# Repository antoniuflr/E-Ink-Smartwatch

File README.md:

# InkTime Smartwatch
The low-powered open-source e-paper watch.

## Final Assembly

## Block Diagram

## Bill of Materials
| Ref | Componenta | Valoare | JLC Parts | Datasheet |
|-----|------------|---------|-----------|-----------|
| U1 | nRF52840 | $5.14 | [JLC](https://jlcpcb.com/parts/componentSearch?searchTxt=nRF52840-QF) | [DS](https://jlcpcb.com/api/file/downloadByFileSystemAccessId/8589839228197629952) |
| J1 | 503480-2400 | $0.84 | [JLC](https://jlcpcb.com/partdetail/MOLEX-5034802400/C122434) | [DS](https://www.molex.com/content/dam/molex/molex-dot-com/products/automated/en-us/salesdrawingpdf/503/503480/5034802400_sd.pdf?inline) |
| IC1 | BQ25180YBGR | $2.01 | [JLC](https://jlcpcb.com/partdetail/TexasInstruments-BQ25180YBGR/C3682423) | [DS](https://www.ti.com/cn/lit/gpn/bq25180) |
| X2 | FC-135_32.7680KA-A3 | $0.2677 | [JLC](https://jlcpcb.com/partdetail/SeikoEpson-FC_135_32_7680KAA3/C2650472) | [DS](https://jlcpcb.com/partdetail/SeikoEpson-FC_135_32_7680KAA3/C2650472) |
| Q1 | DMG2305UX-7 | $0.10 | [JLC](https://jlcpcb.com/partdetail/DiodesIncorporated-DMG2305UX7/C150470) | [DS](https://jlcpcb.com/api/file/downloadByFileSystemAccessId/8560079443617075200) |
| D5 | MBR0530 | $0.03 | [JLC](https://jlcpcb.com/partdetail/78464-MBR0530/C77336) | [DS](https://jlcpcb.com/api/file/downloadByFileSystemAccessId/8586175081181818880) |
| IC9 | RT6160 | $0.56 | [JLC](https://jlcpcb.com/partdetail/RichtekTech-RT6160AWSC/C7065276) | [DS](https://jlcpcb.com/api/file/downloadByFileSystemAccessId/8600398231234883584) |
| L2 | RC0402JR-070RL | $0.01 | [JLC](https://jlcpcb.com/partdetail/YAGEO-RC0402JR070RL/C60485) | [DS](https://jlcpcb.com/api/file/downloadByFileSystemAccessId/8717146932348461056) |
| J4 | KH-TYPE-C-16P | $0.08 | [JLC](https://jlcpcb.com/partdetail/Shenzhen_KinghelmElec-KH_TYPE_C16P/C709357) | [DS](https://jlcpcb.com/api/file/downloadByFileSystemAccessId/8588905154556923904) |
| SWD | TC2030-IDC | $100.26 | [JLC](https://jlcpcb.com/partdetail/MicrochipTech-TC2030_CLIP3PACK/C5444772) | [DS](https://www.lcsc.com/datasheet/lcsc_datasheet_2403201318_Microchip-Tech-TC2030-CLIP-3PACK_C5444772.pdf) |
| U3 | MAX17048G-T10 | $2.44 | [JLC](https://jlcpcb.com/partdetail/2777647-MAX17048GT10/C2682616) | [DS](https://jlcpcb.com/api/file/downloadByFileSystemAccessId/8588907428524003328) |
| D3 | USBLC6-2SC6Y | $0.24 | [JLC](https://jlcpcb.com/partdetail/STMicroelectronics-USBLC62SC6Y/C2969755) | [DS](https://jlcpcb.com/api/file/downloadByFileSystemAccessId/8603165824304111616) |
| L3 | RC0402JR-070RL | $0.01 | [JLC](https://jlcpcb.com/partdetail/YAGEO-RC0402JR070RL/C60485) | [DS](https://jlcpcb.com/api/file/downloadByFileSystemAccessId/8717146932348461056) |
| X1 | NX2016SA-32MHZ-EXS00A-CS11336 | $9.04 | [JLC](https://jlcpcb.com/partdetail/NDK-NX2016SA_32MHZ_EXS00ACS11336/C6134317) | [DS](https://jlcpcb.com/api/file/downloadByFileSystemAccessId/8603064888214908928) |
| ANT1 | 2450AT18B100E | $1.03 | [JLC](https://jlcpcb.com/partdetail/JohansonDielectrics-2450AT18B100E/C2917717) | [DS](https://jlcpcb.com/api/file/downloadByFileSystemAccessId/8588940948130156544) |
| Q3 | SI1308EDL-T1-GE3 | $0.18 | [JLC](https://jlcpcb.com/partdetail/VishayIntertech-SI1308EDL_T1GE3/C469327) | [DS](https://jlcpcb.com/api/file/downloadByFileSystemAccessId/8588884784742846464) |
| IC2 | DRV2605YZFR | $1.31 | [JLC](https://jlcpcb.com/partdetail/TexasInstruments-DRV2605YZFR/C81079) | [DS](https://www.ti.com/cn/lit/gpn/drv2605) |
| D2 | MBR0530 | $0.03 | [JLC](https://jlcpcb.com/partdetail/78464-MBR0530/C77336) | [DS](https://jlcpcb.com/api/file/downloadByFileSystemAccessId/8586175081181818880) |
| IC3 | BMA423 | $11.30 | [JLC](https://jlcpcb.com/partdetail/BoschSensortec-BMA423/C189517) | [DS](https://jlcpcb.com/api/file/downloadByFileSystemAccessId/8588894317147017216) |
| L7 | MLP2016SR47MT0S1 | $0.10 | [JLC](https://jlcpcb.com/partdetail/TDK-MLP2016SR47MT0S1/C87545) | [DS](https://jlcpcb.com/api/file/downloadByFileSystemAccessId/8588933367512879104) |
| L5 | 744043680 | $9.53 | [JLC](https://jlcpcb.com/partdetail/WurthElektronik-744043680/C2045671) | [DS](https://www.we-online.com/components/products/datasheet/744043680.pdf) |
| D4 | MBR0530 | $0.03 | [JLC](https://jlcpcb.com/partdetail/78464-MBR0530/C77336) | [DS](https://jlcpcb.com/api/file/downloadByFileSystemAccessId/8586175081181818880) |

## Hardware Overview
- `nRF52840 (U1)`: main MCU; handles BLE, USB, timekeeping, button logic, display refresh, and power-state control.
- `BQ25180 (IC1)`: LiPo charger and power-path manager; takes `VBUS` from USB-C, charges the battery, and exposes status on `I2C` plus `PMIC_INT`.
- `RT6160 (IC9)`: buck-boost regulator; converts the charger `SYS/VREG` rail into the stable `3V3` rail used by the digital system.
- `BMA421 IMU (IC3 schematic value)`: accelerometer/pedometer connected over `I2C`; `INT1` and `INT2` wake the MCU on motion and step events.
- `MAX17048 (U3)`: fuel gauge connected to raw `VBAT`; reports battery state over `I2C` and raises `ALERT` on low-battery thresholds.
- `DRV2605L (IC2)`: haptic driver on `I2C`; enabled by `HAPTIC_EN` and drives the vibration motor through `OUT+` and `OUT-`.
- `E-paper display (J1)`: connected through `SPI` (`SCK`, `MOSI`, `CS`) plus `DC`, `RST`, and `BUSY`; uses a dedicated switched rail so the panel can be fully turned off between updates.
- `USB-C + ESD (J4 + D3)`: provides `VBUS` power, USB `D+ / D-`, and surge protection for the MCU USB interface.
- `Debug + bring-up`: Tag-Connect `TC2030` exposes `SWDIO`, `SWDCLK`, and `RESET` for flashing and recovery.
- `Power strategy`: `USB-C 5V -> BQ25180 -> RT6160 -> 3V3`; the watch stays in low-power sleep most of the time, wakes on RTC/buttons/interrupts, and uses e-paper partial refreshes to keep average power low.
- `Communication`: shared `I2C` bus for PMIC, regulator, IMU, fuel gauge, and haptic driver; `SPI` for the display; `BLE` for the phone link.

## Exploded Assembly

## nRF52840 Pin Mapping
| nRF52840 Pin | Signal | Component | Interface |
|--------------|--------|-----------|-----------|
| P0.00/XL1 | XL1 | Crystal X2 (32.768kHz) | XTAL |
| P0.01/XL2 | XL2 | Crystal X2 (32.768kHz) | XTAL |
| P0.02/AIN0 | SCK | E-Paper (J1 FPC) | SPI SCK |
| P0.03/AIN1 | MOSI | E-Paper (J1 FPC) | SPI MOSI |
| P0.05/AIN3 | EPD_CS | E-Paper (J1 FPC) | SPI CS |
| P0.06 | SDA | BMA421, BQ25180, RT6160, MAX17048, DRV2605 | I2C SDA |
| P0.07 | SCL | BMA421, BQ25180, RT6160, MAX17048, DRV2605 | I2C SCL |
| P0.08 | IMU_INT1 | BMA421 | GPIO Input |
| P1.08 | IMU_INT2 | BMA421 | GPIO Input |
| P0.10/NFC2 | ALERT | MAX17048 | GPIO Input |
| P0.11 | PMIC_INT | BQ25180 | GPIO Input |
| P0.12 | HAPTIC_EN | DRV2605 | GPIO Output |
| P0.13 | SW_UP | Up button | GPIO Input |
| P0.14 | SW_ENT | Enter button | GPIO Input |
| P0.15 | EPD_DC | E-Paper (J1 FPC) | SPI DC |
| P0.16 | EPD_RST | E-Paper (J1 FPC) | GPIO Output |
| P0.17 | EPD_BUSY | E-Paper (J1 FPC) | GPIO Input |
| P0.18/RESET | RESET | TC2030-IDC | SWD / GPIO |
| P1.02 | SW_DN | Down button | GPIO Input |
| VBUS | VBUS | USB-C (J4) | Power |
| D- | D- | USB-C (J4) / USBLC6 | USB |
| D+ | D+ | USB-C (J4) / USBLC6 | USB |
| SWDCLK | SWDCLK | TC2030-IDC | SWD |
| SWDIO | SWDIO | TC2030-IDC | SWD |
| ANT | RF | 2450AT18B100E antenna | RF |

## PCB Views

## Log Journal
- Grouping IC's with their respective passive components.
- Placing them so ratsnest is as straight as possible on the board.
- Route critical signal first.
- Route power.
- Route rest.

Clean ERC. Ignored micro-via errors in DRC because without them routing the BGA would have been impossible.

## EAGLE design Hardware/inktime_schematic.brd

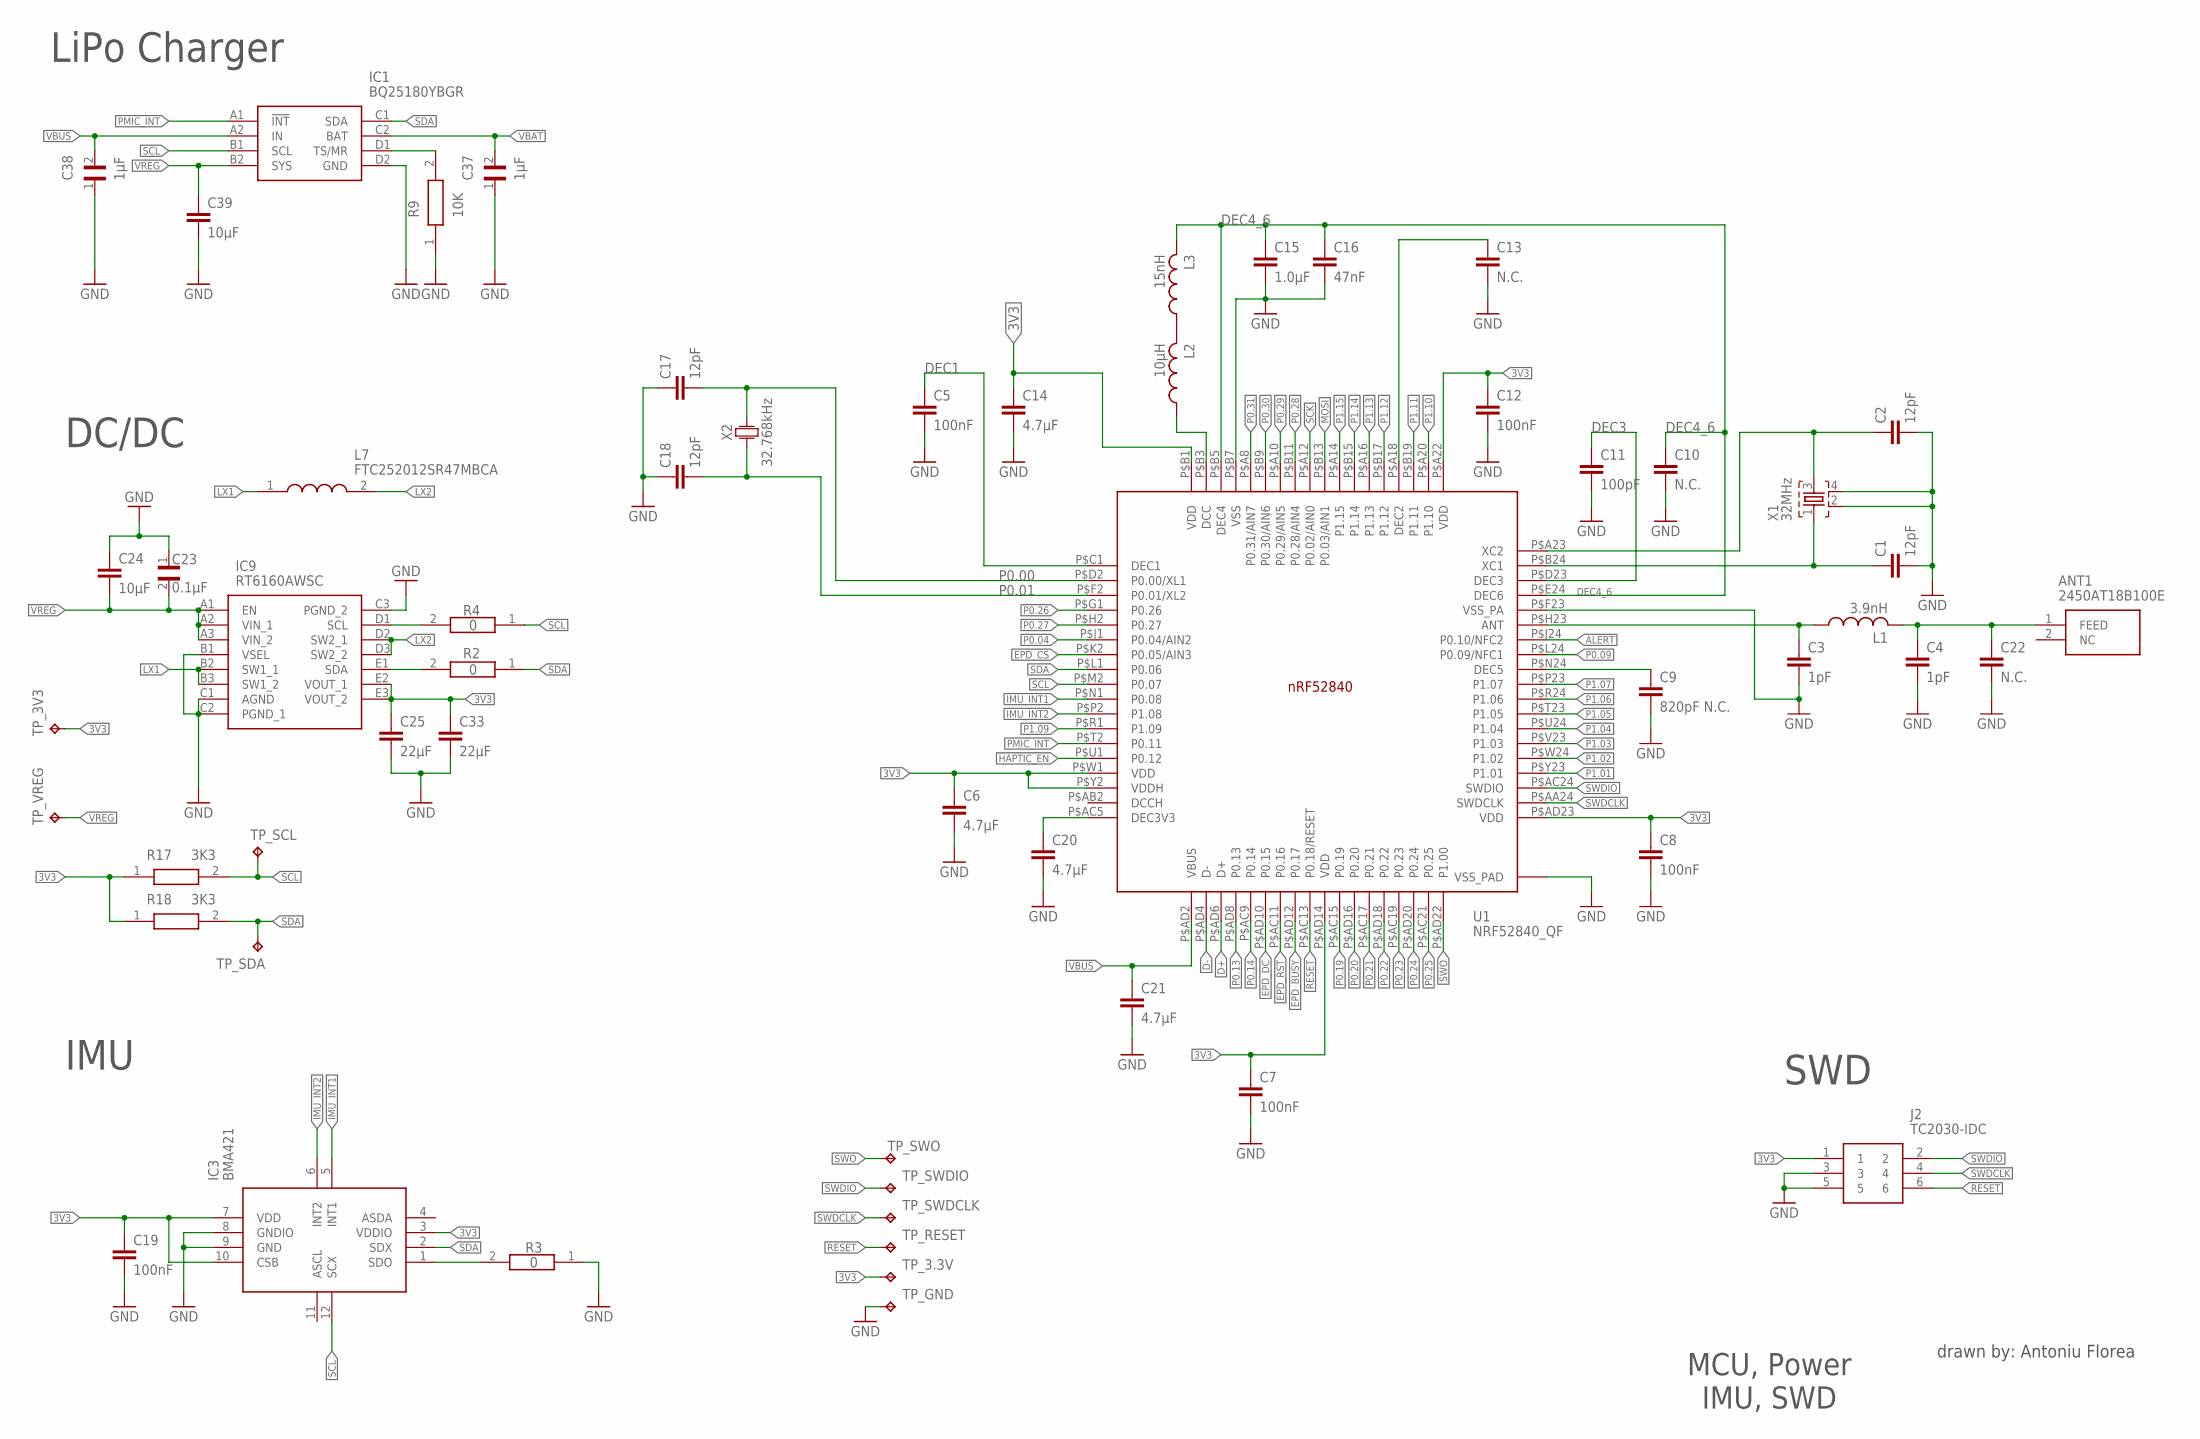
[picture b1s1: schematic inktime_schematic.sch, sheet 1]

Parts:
ANT1: 2450AT18B100E; 2450AT18B100E_ANTC3216X140N
C1, C2, C17, C18: 12pF; NORDIC_NRF_3_RESC0201_L
C3, C4: 1pF; NORDIC_NRF_3_RESC0201_L
C5, C7, C8, C12, C19: 100nF; NORDIC_NRF_3_RESC0201_L
C6, C14, C20, C21: 4.7μF; NORDIC_NRF_3_RESC0402_L
C9: 820pF N.C.; NORDIC_NRF_3_RESC0201_L
C10, C13, C22: N.C.; NORDIC_NRF_3_RESC0201_L
C11: 100pF; NORDIC_NRF_3_RESC0201_L
C15: 1.0μF; NORDIC_NRF_3_RESC0402_L
C16: 47nF; NORDIC_NRF_3_RESC0201_L
C23: 0.1μF; GRM011R60J152KE01L_2_CAPC0201X13N
C24, C39: 10μF; NORDIC_NRF_3_RESC0402_L
C25, C33: 22μF; NORDIC_NRF_3_RESC0402_L
C37, C38: 1μF; GRM011R60J152KE01L_2_CAPC0201X13N
IC1: BQ25180YBGR; BQ25180YBGR_BGA8C40P2X4_100X155X50
IC3: BMA421; BMA423_BMA423
IC9: RT6160AWSC; RT6160AWSC_BGA15C40P3X5_140X230X60
J2: TC2030-IDC; TC2030-IDC_TC2030IDC
L1: 3.9nH; NORDIC_NRF_2_RESC0201_L
L2: 10μH; NORDIC_NRF_2_RESC0201_L
L3: 15nH; NORDIC_NRF_2_RESC0201_L
L7: FTC252012SR47MBCA; MLP2016SR47MT0S1_INDC2016X100N
R2, R3, R4: 0; CPF0201D7K68C1_0201
R9: 10K; ERA-1AEB3401C_0201
R17, R18: 3K3; CPF0201D7K68C1_0201
TP_3.3V, TP_3V3: HECTOR_WATCH_1_TPTP20R; HECTOR_WATCH_1_TP20R
TP_GND: HECTOR_WATCH_1_TPTP20R; HECTOR_WATCH_1_TP20R
TP_RESET: HECTOR_WATCH_1_TPTP20R; HECTOR_WATCH_1_TP20R
TP_SCL: HECTOR_WATCH_1_TPTP20R; HECTOR_WATCH_1_TP20R
TP_SDA: HECTOR_WATCH_1_TPTP20R; HECTOR_WATCH_1_TP20R
TP_SWDCLK: HECTOR_WATCH_1_TPTP20R; HECTOR_WATCH_1_TP20R
TP_SWDIO: HECTOR_WATCH_1_TPTP20R; HECTOR_WATCH_1_TP20R
TP_SWO: HECTOR_WATCH_1_TPTP20R; HECTOR_WATCH_1_TP20R
TP_VREG: HECTOR_WATCH_1_TPTP20R; HECTOR_WATCH_1_TP20R
U1: NRF52840_QF; NORDIC_NRF_4_AQFN50P700X700X85_HS-74N
X1: 32MHz; NORDIC_NRF_BT-XTAL_2016_N
X2: 32.768kHz; XTAL330X1051X90N

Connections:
3V3: C6.1, C7.1, C8.1, C12.1, C14.1, C19.1, C25.1, C33.1, IC3.3 (VDDIO), IC3.7 (VDD), IC3.10 (CSB), IC9.E2 (VOUT_1), IC9.E3 (VOUT_2), J2.1, R17.1, R18.1, TP_3.3V.TP, TP_3V3.TP, U1.P$A22 (VDD), U1.P$AD14 (VDD), U1.P$AD23 (VDD), U1.P$B1 (VDD), U1.P$W1 (VDD), U1.P$Y2 (VDDH); also elsewhere on the board
ALERT: U1.P$J24 (P0.10/NFC2); also elsewhere on the board
D+: U1.P$AD6 (D+); also elsewhere on the board
D-: U1.P$AD4 (D-); also elsewhere on the board
DEC1: C5.1, U1.P$C1 (DEC1)
DEC3: C11.1, U1.P$D23 (DEC3)
DEC4_6: C10.1, C15.1, C16.1, L3.2, U1.P$B5 (DEC4), U1.P$E24 (DEC6)
EPD_BUSY: U1.P$AD12 (P0.17); also elsewhere on the board
EPD_CS: U1.P$K2 (P0.05/AIN3); also elsewhere on the board
EPD_DC: U1.P$AD10 (P0.15); also elsewhere on the board
EPD_RST: U1.P$AC11 (P0.16); also elsewhere on the board
GND: C1.2, C2.2, C3.2, C4.2, C5.2, C6.2, C7.2, C8.2, C9.2, C10.2, C11.2, C12.2, C13.2, C14.2, C15.2, C16.2, C17.1, C18.1, C19.2, C20.2, C21.2, C22.2, C23.1, C24.1, C25.2, C33.2, C37.1, C38.1, C39.2, IC1.D2 (GND), IC3.8 (GNDIO), IC3.9 (GND), IC9.B1 (VSEL), IC9.C1 (AGND), IC9.C2 (PGND_1), IC9.C3 (PGND_2), J2.3, J2.5, R3.1, R9.1, TP_GND.TP, U1.P$74 (VSS_PAD), U1.P$75 (VSS_PAD), U1.P$76 (VSS_PAD), U1.P$77 (VSS_PAD), U1.P$78 (VSS_PAD), U1.P$79 (VSS_PAD), U1.P$80 (VSS_PAD), U1.P$81 (VSS_PAD), U1.P$82 (VSS_PAD), U1.P$83 (VSS_PAD), U1.P$84 (VSS_PAD), U1.P$85 (VSS_PAD), U1.P$86 (VSS_PAD), U1.P$87 (VSS_PAD), U1.P$88 (VSS_PAD), U1.P$89 (VSS_PAD), U1.P$90 (VSS_PAD), U1.P$B7 (VSS), U1.P$F23 (VSS_PA), X1.2, X1.4; also elsewhere on the board
HAPTIC_EN: U1.P$U1 (P0.12); also elsewhere on the board
IMU_INT1: IC3.5 (INT1), U1.P$N1 (P0.08)
IMU_INT2: IC3.6 (INT2), U1.P$P2 (P1.08)
LX1: IC9.B2 (SW1_1), IC9.B3 (SW1_2), L7.1
LX2: IC9.D2 (SW2_1), IC9.D3 (SW2_2), L7.2
MOSI: U1.P$B13 (P0.03/AIN1); also elsewhere on the board
unnamed: C1.1, U1.P$B24 (XC1), X1.1
unnamed: C3.1, L1.1, U1.P$H23 (ANT)
unnamed: C2.1, U1.P$A23 (XC2), X1.3
unnamed: ANT1.1 (FEED), C4.1, C22.1, L1.2
unnamed: C9.1, U1.P$N24 (DEC5)
unnamed: C20.1, U1.P$AC5 (DEC3V3)
unnamed: L2.1, U1.P$B3 (DCC)
unnamed: L2.2, L3.1
unnamed: IC9.D1 (SCL), R4.2
unnamed: C13.1, U1.P$A18 (DEC2)
unnamed: IC1.D1 (TS/MR), R9.2
unnamed: IC9.E1 (SDA), R2.2
unnamed: IC3.1 (SDO), R3.2
P0.00: C17.2, U1.P$D2 (P0.00/XL1), X2.2
P0.01: C18.2, U1.P$F2 (P0.01/XL2), X2.1
P0.04: U1.P$J1 (P0.04/AIN2)
P0.09: U1.P$L24 (P0.09/NFC1)
P0.13: U1.P$AD8 (P0.13); also elsewhere on the board
P0.14: U1.P$AC9 (P0.14); also elsewhere on the board
P0.19: U1.P$AC15 (P0.19)
P0.20: U1.P$AD16 (P0.20)
P0.21: U1.P$AC17 (P0.21)
P0.22: U1.P$AD18 (P0.22)
P0.23: U1.P$AC19 (P0.23)
P0.24: U1.P$AD20 (P0.24)
P0.25: U1.P$AC21 (P0.25)
P0.26: U1.P$G1 (P0.26)
P0.27: U1.P$H2 (P0.27)
P0.28: U1.P$B11 (P0.28/AIN4)
P0.29: U1.P$A10 (P0.29/AIN5)
P0.30: U1.P$B9 (P0.30/AIN6)
P0.31: U1.P$A8 (P0.31/AIN7)
P1.01: U1.P$Y23 (P1.01); also elsewhere on the board
P1.02: U1.P$W24 (P1.02); also elsewhere on the board
P1.03: U1.P$V23 (P1.03)
P1.04: U1.P$U24 (P1.04)
P1.05: U1.P$T23 (P1.05)
P1.06: U1.P$R24 (P1.06)
P1.07: U1.P$P23 (P1.07)
P1.09: U1.P$R1 (P1.09)
P1.10: U1.P$A20 (P1.10)
P1.11: U1.P$B19 (P1.11)
P1.12: U1.P$B17 (P1.12)
P1.13: U1.P$A16 (P1.13)
P1.14: U1.P$B15 (P1.14)
P1.15: U1.P$A14 (P1.15)
PMIC_INT: IC1.A1 (!INT), U1.P$T2 (P0.11)
RESET: J2.6, TP_RESET.TP, U1.P$AC13 (P0.18/RESET)
SCK: U1.P$A12 (P0.02/AIN0); also elsewhere on the board
SCL: IC1.B1 (SCL), IC3.12 (SCX), R4.1, R17.2, TP_SCL.TP, U1.P$M2 (P0.07); also elsewhere on the board
SDA: IC1.C1 (SDA), IC3.2 (SDX), R2.1, R18.2, TP_SDA.TP, U1.P$L1 (P0.06); also elsewhere on the board
SWDCLK: J2.4, TP_SWDCLK.TP, U1.P$AA24 (SWDCLK)
SWDIO: J2.2, TP_SWDIO.TP, U1.P$AC24 (SWDIO)
SWO: TP_SWO.TP, U1.P$AD22 (P1.00)
VBAT: C37.2, IC1.C2 (BAT); also elsewhere on the board
VBUS: C21.1, C38.2, IC1.A2 (IN), U1.P$AD2 (VBUS); also elsewhere on the board
VREG: C23.2, C24.2, C39.1, IC1.B2 (SYS), IC9.A1 (EN), IC9.A2 (VIN_1), IC9.A3 (VIN_2), TP_VREG.TP

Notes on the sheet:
LiPo Charger
DC/DC
IMU
SWD
MCU, Power IMU, SWD
drawn by: Antoniu Florea

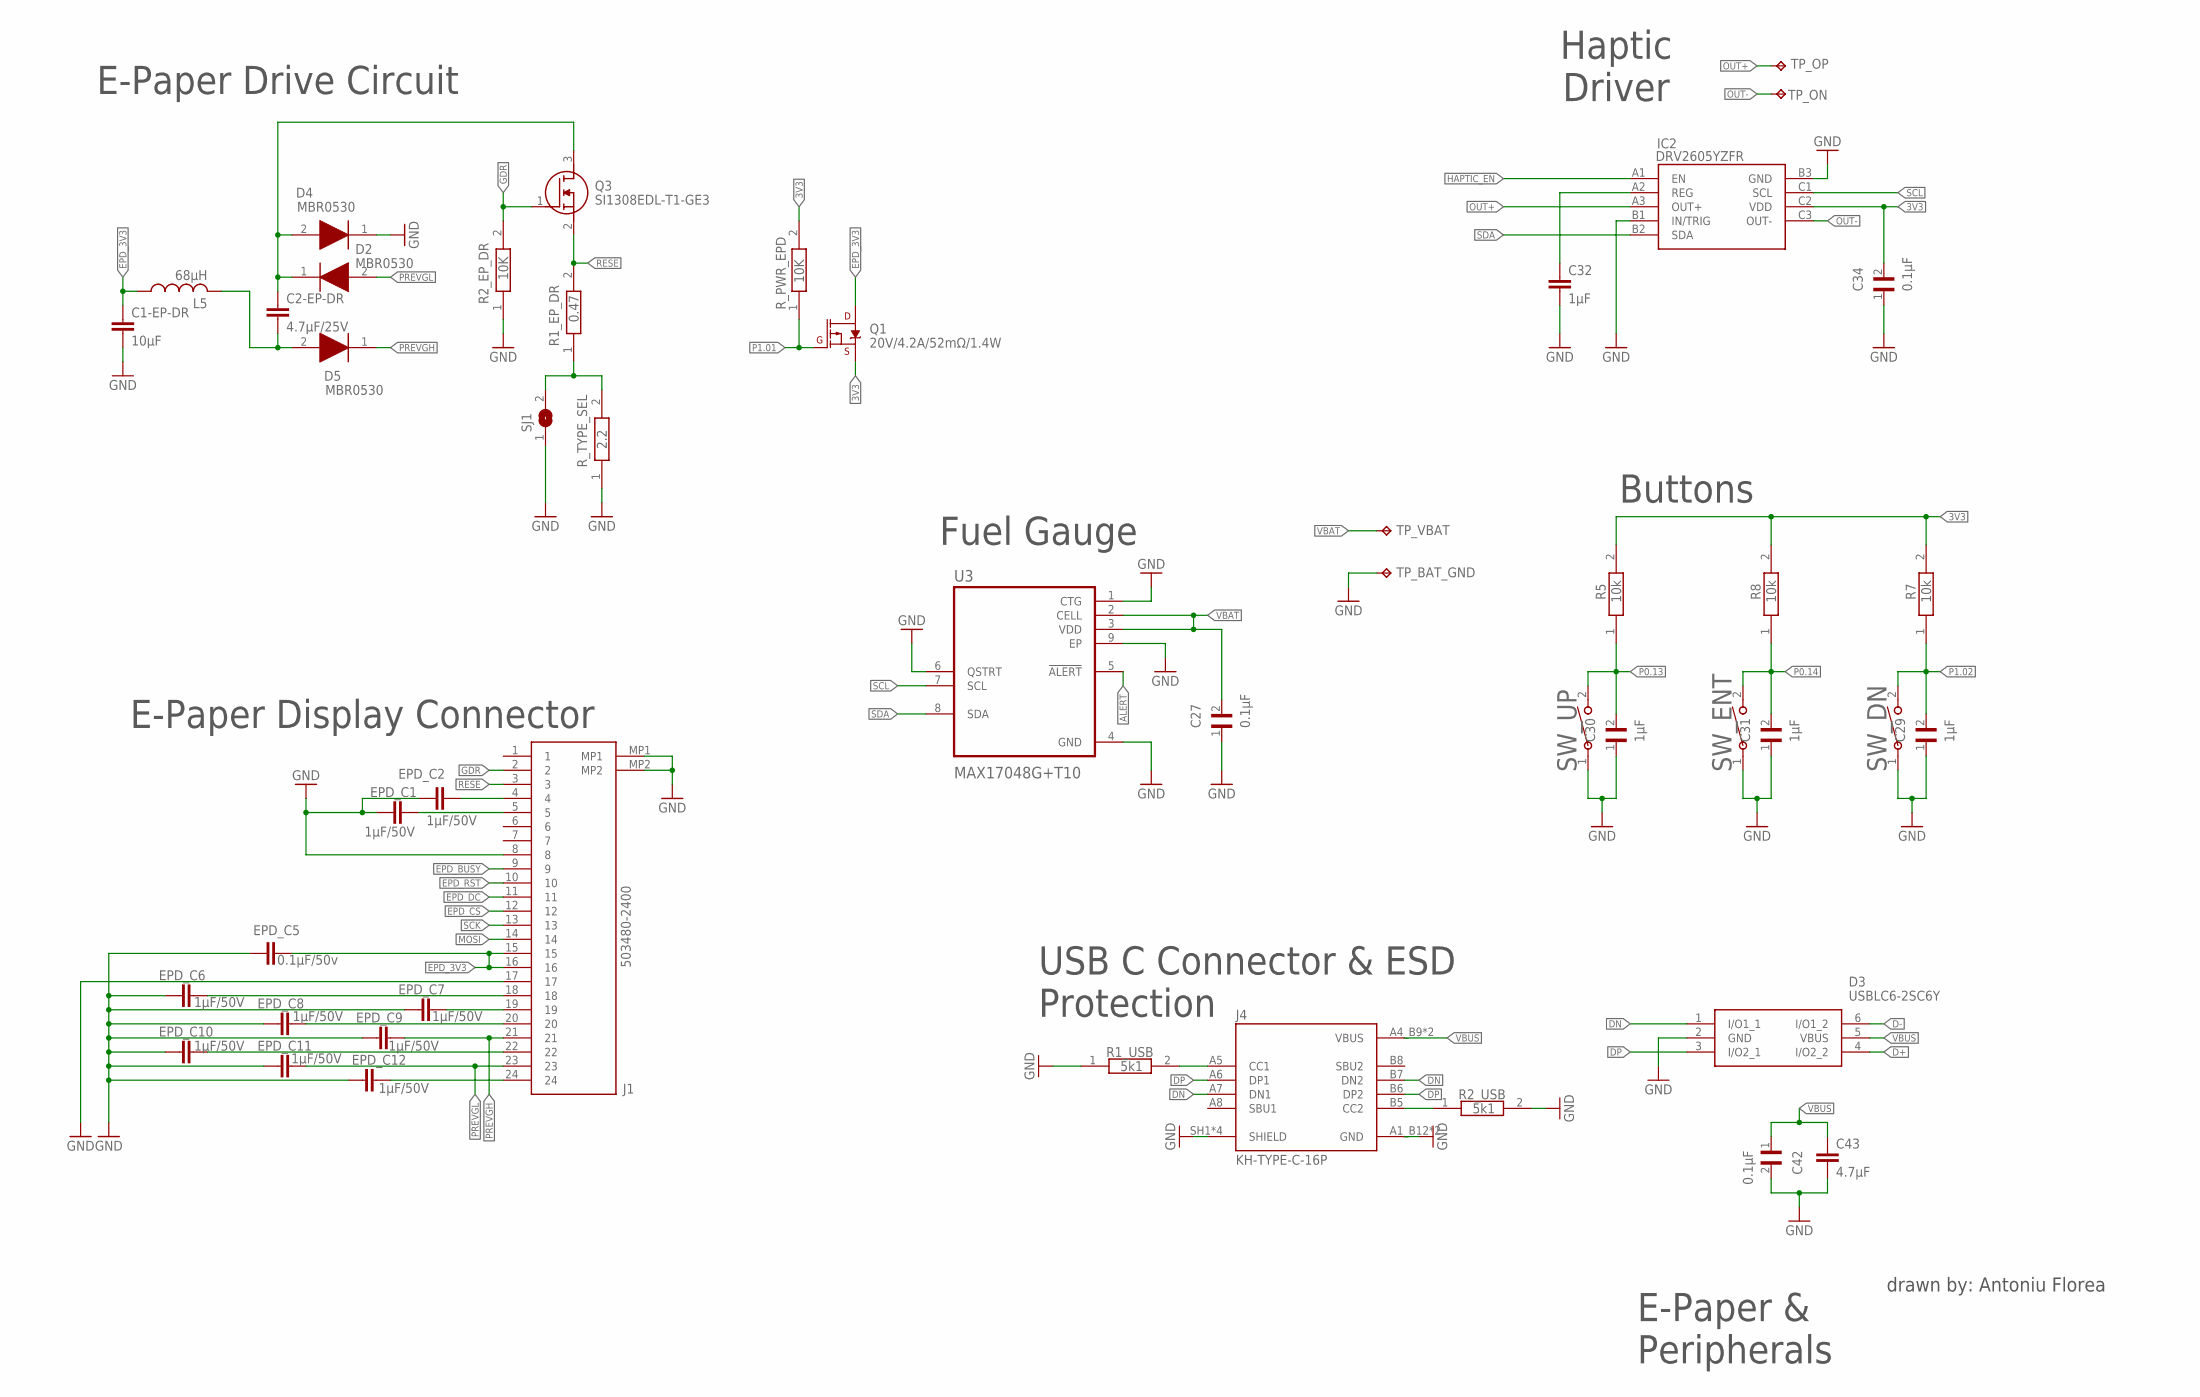
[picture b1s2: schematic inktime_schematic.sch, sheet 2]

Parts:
C1-EP-DR: 10μF; NORDIC_NRF_3_RESC0402_L
C2-EP-DR: 4.7μF/25V; NORDIC_NRF_3_RESC0402_L
C27, C34, C42: 0.1μF; GRM011R60J152KE01L_2_CAPC0201X13N
C29, C30, C31: 1μF; GRM011R60J152KE01L_2_CAPC0201X13N
C32: 1μF; NORDIC_NRF_3_RESC0402_L
C43: 4.7μF; NORDIC_NRF_3_RESC0402_L
D2, D4, D5: MBR0530; ESP32_C6_LIBRARY_5_SOD3716X135N
D3: USBLC6-2SC6Y; ESP32_C6_LIBRARY_3_SOT95P280X145-6N
EPD_C1, EPD_C2, EPD_C6, EPD_C7, EPD_C8, EPD_C9, EPD_C10, EPD_C11, EPD_C12: 1μF/50V; NORDIC_NRF_3_RESC0402_L
EPD_C5: 0.1μF/50v; NORDIC_NRF_3_RESC0201_L
IC2: DRV2605YZFR; DRV2605YZFR_BGA9C50P3X3_144X144X62
J1: 503480-2400; 503480-2400_5034802400
J4: KH-TYPE-C-16P; KH-TYPE-C-16P_KINGHELM_KH-TYPE-C-16P
L5: 68μH; NORDIC_NRF_2_RESC0402_L
Q1: 20V/4.2A/52mΩ/1.4W; ESP32_C6_LIBRARY_4_ESP32_C6_LIBRARY_4_ESP32_C6_LIBRARY_4_ES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
Q3: SI1308EDL-T1-GE3; ESP32_C6_LIBRARY_6_SOT65P210X110-3N
R1_EP_DR: 0.47; CPF0201D7K68C1_0201
R1_USB, R2_USB: 5k1; ERA-1AEB3401C_0201
R2_EP_DR: 10K; CPF0201D7K68C1_0201
R5, R7, R8: 10k; CPF0201D7K68C1_0201
R_PWR_EPD: 10K; CPF0201D7K68C1_0201
R_TYPE_SEL: 2.2; CPF0201D7K68C1_0201
SJ1: ESP32_C6_LIBRARY_7_JUMPER_SJ
SW_DN: 2025-10-22_07-23-44_LIBRARY_EVP-AKE31ASW_EVP-AKE3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; 2025-10-22_07-23-44_LIBRARY_SW_EVP-AKE31A_PAN
SW_ENT: 2025-10-22_07-23-44_LIBRARY_EVP-AKE31ASW_EVP-AKE3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; 2025-10-22_07-23-44_LIBRARY_SW_EVP-AKE31A_PAN
SW_UP: 2025-10-22_07-23-44_LIBRARY_EVP-AKE31ASW_EVP-AKE3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; 2025-10-22_07-23-44_LIBRARY_SW_EVP-AKE31A_PAN
TP_BAT_GND: HECTOR_WATCH_1_TPTP20R; HECTOR_WATCH_1_TP20R
TP_ON: HECTOR_WATCH_1_TPTP20R; HECTOR_WATCH_1_TP20R
TP_OP: HECTOR_WATCH_1_TPTP20R; HECTOR_WATCH_1_TP20R
TP_VBAT: HECTOR_WATCH_1_TPTP20R; HECTOR_WATCH_1_TP20R
U3: MAX17048G+T10; ESP32_C6_LIBRARY_SON50P200X200X80-9N

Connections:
3V3: C34.2, IC2.C2 (VDD), Q1.2 (S), R5.2, R7.2, R8.2, R_PWR_EPD.2; also elsewhere on the board
ALERT: U3.5 (!ALERT); also elsewhere on the board
D+: D3.4 (I/O2_2); also elsewhere on the board
D-: D3.6 (I/O1_2); also elsewhere on the board
DN: D3.1 (I/O1_1), J4.A7 (DN1), J4.B7 (DN2)
DP: D3.3 (I/O2_1), J4.A6 (DP1), J4.B6 (DP2)
EPD_3V3: C1-EP-DR.1, EPD_C5.2, J1.15, J1.16, L5.1, Q1.3 (D)
EPD_BUSY: J1.9; also elsewhere on the board
EPD_CS: J1.12; also elsewhere on the board
EPD_DC: J1.11; also elsewhere on the board
EPD_RST: J1.10; also elsewhere on the board
GDR: J1.2, Q3.1 (G), R2_EP_DR.2
GND: C1-EP-DR.2, C27.1, C29.1, C30.1, C31.1, C32.2, C34.1, C42.2, C43.2, D3.2 (GND), D4.1 (K), EPD_C1.2, EPD_C2.2, EPD_C5.1, EPD_C6.2, EPD_C7.2, EPD_C8.2, EPD_C9.2, EPD_C10.2, EPD_C11.2, EPD_C12.2, IC2.B1 (IN/TRIG), IC2.B3 (GND), J1.8, J1.17, J1.MP1, J1.MP2, J4.A1_B12 (GND), J4.A12_B1 (GND), J4.SH1 (SHIELD), J4.SH2 (SHIELD), J4.SH3 (SHIELD), J4.SH4 (SHIELD), R1_USB.1, R2_EP_DR.1, R2_USB.2, R_TYPE_SEL.1, SJ1.1, SW_DN.1, SW_ENT.1, SW_UP.1, TP_BAT_GND.TP, U3.1 (CTG), U3.4 (GND), U3.6 (QSTRT), U3.9 (EP); also elsewhere on the board
HAPTIC_EN: IC2.A1 (EN); also elsewhere on the board
MOSI: J1.14; also elsewhere on the board
unnamed: C2-EP-DR.2, D5.2 (A), L5.2
unnamed: C2-EP-DR.1, D2.1 (K), D4.2 (A), Q3.3 (D)
unnamed: EPD_C2.1, J1.4
unnamed: R1_EP_DR.1, R_TYPE_SEL.2, SJ1.2
unnamed: C32.1, IC2.A2 (REG)
unnamed: EPD_C1.1, J1.5
unnamed: EPD_C6.1, J1.18
unnamed: EPD_C7.1, J1.19
unnamed: EPD_C8.1, J1.20
unnamed: J4.A5 (CC1), R1_USB.2
unnamed: EPD_C10.1, J1.22
unnamed: EPD_C12.1, J1.24
unnamed: J4.B5 (CC2), R2_USB.1
OUT+: IC2.A3 (OUT+), TP_OP.TP
OUT-: IC2.C3 (OUT-), TP_ON.TP
P0.13: C30.2, R5.1, SW_UP.2; also elsewhere on the board
P0.14: C31.2, R8.1, SW_ENT.2; also elsewhere on the board
P1.01: Q1.1 (G), R_PWR_EPD.1; also elsewhere on the board
P1.02: C29.2, R7.1, SW_DN.2; also elsewhere on the board
PREVGH: D5.1 (K), EPD_C9.1, J1.21
PREVGL: D2.2 (A), EPD_C11.1, J1.23
RESE: J1.3, Q3.2 (S), R1_EP_DR.2
SCK: J1.13; also elsewhere on the board
SCL: IC2.C1 (SCL), U3.7 (SCL); also elsewhere on the board
SDA: IC2.B2 (SDA), U3.8 (SDA); also elsewhere on the board
VBAT: C27.2, TP_VBAT.TP, U3.2 (CELL), U3.3 (VDD); also elsewhere on the board
VBUS: C42.1, C43.1, D3.5 (VBUS), J4.A4_B9 (VBUS), J4.A9_B4 (VBUS); also elsewhere on the board

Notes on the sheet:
E-Paper Drive Circuit
Haptic Driver
E-Paper Display Connector
Fuel Gauge
Buttons
USB C Connector & ESD Protection
E-Paper & Peripherals
drawn by: Antoniu Florea

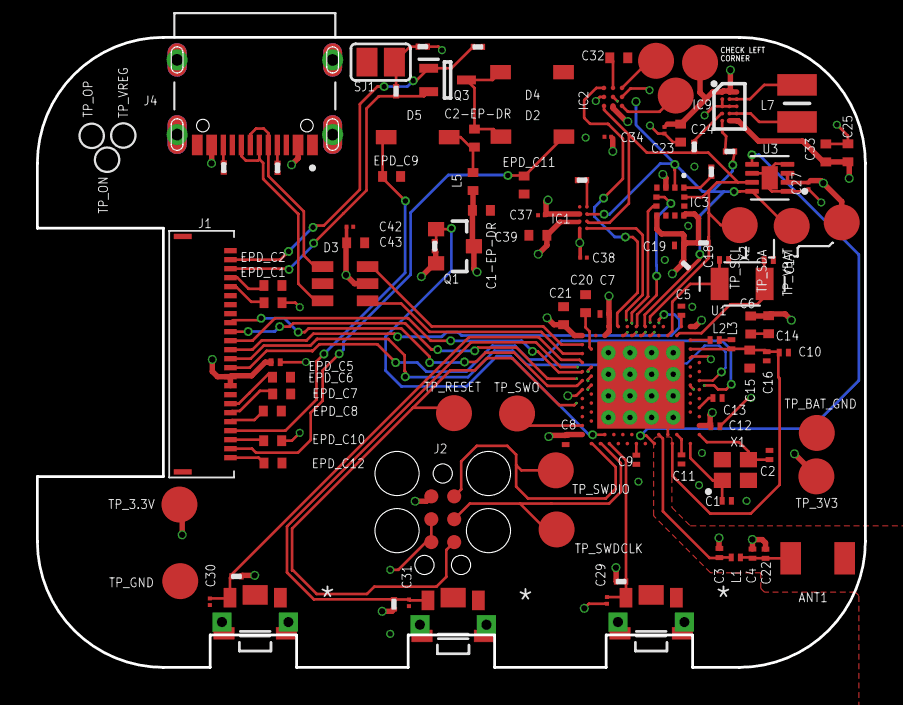
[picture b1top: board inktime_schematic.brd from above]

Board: 4 copper layers, 46.0 x 35.0 mm, 105 parts (0 on the bottom side), 70 nets.

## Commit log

2026-04-10 Added files
2026-04-21 Added updated schematic and design.
    Added .sch, .brd and .pdf of schematic fixing issues.
2026-04-21 Updated manufacturing after changes to board.
2026-04-21 Added renders of final product and board.
2026-04-21 Add Apache License 2.0
    Added Apache License 2.0 to the project.
2026-04-21 Added block diagram

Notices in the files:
parts and their libraries:
COPYRIGHT: Copyright (C) 2025 Ultra Librarian. All rights reserved.
